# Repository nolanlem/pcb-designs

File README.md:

# pcb-designs
EAGLE PCB-DESIGN Files for Various Projects

Self-oscillating electromagnetic solenoid pendulums for kinetic art installation. 
+ this scalable circuit controls an array of solenoid electromagnets 
+ oscillatory motion using a a dynamic feedback control system. 
+ see audio-visual documentation [here](https://www.youtube.com/watch?v=IUg8T152WAE)

Magnetic Field -> Variable Frequency Oscillator and Voltage Controlled Amplifier design 
+ This circuit consists of 3 stages: a hall sensor + voltage buffer, sine wave oscillator + voltage buffer, and voltage controlled amplifier with variable signal power gain. 
+ video documentation [here](https://www.youtube.com/watch?v=2vKYp0yhHyw)

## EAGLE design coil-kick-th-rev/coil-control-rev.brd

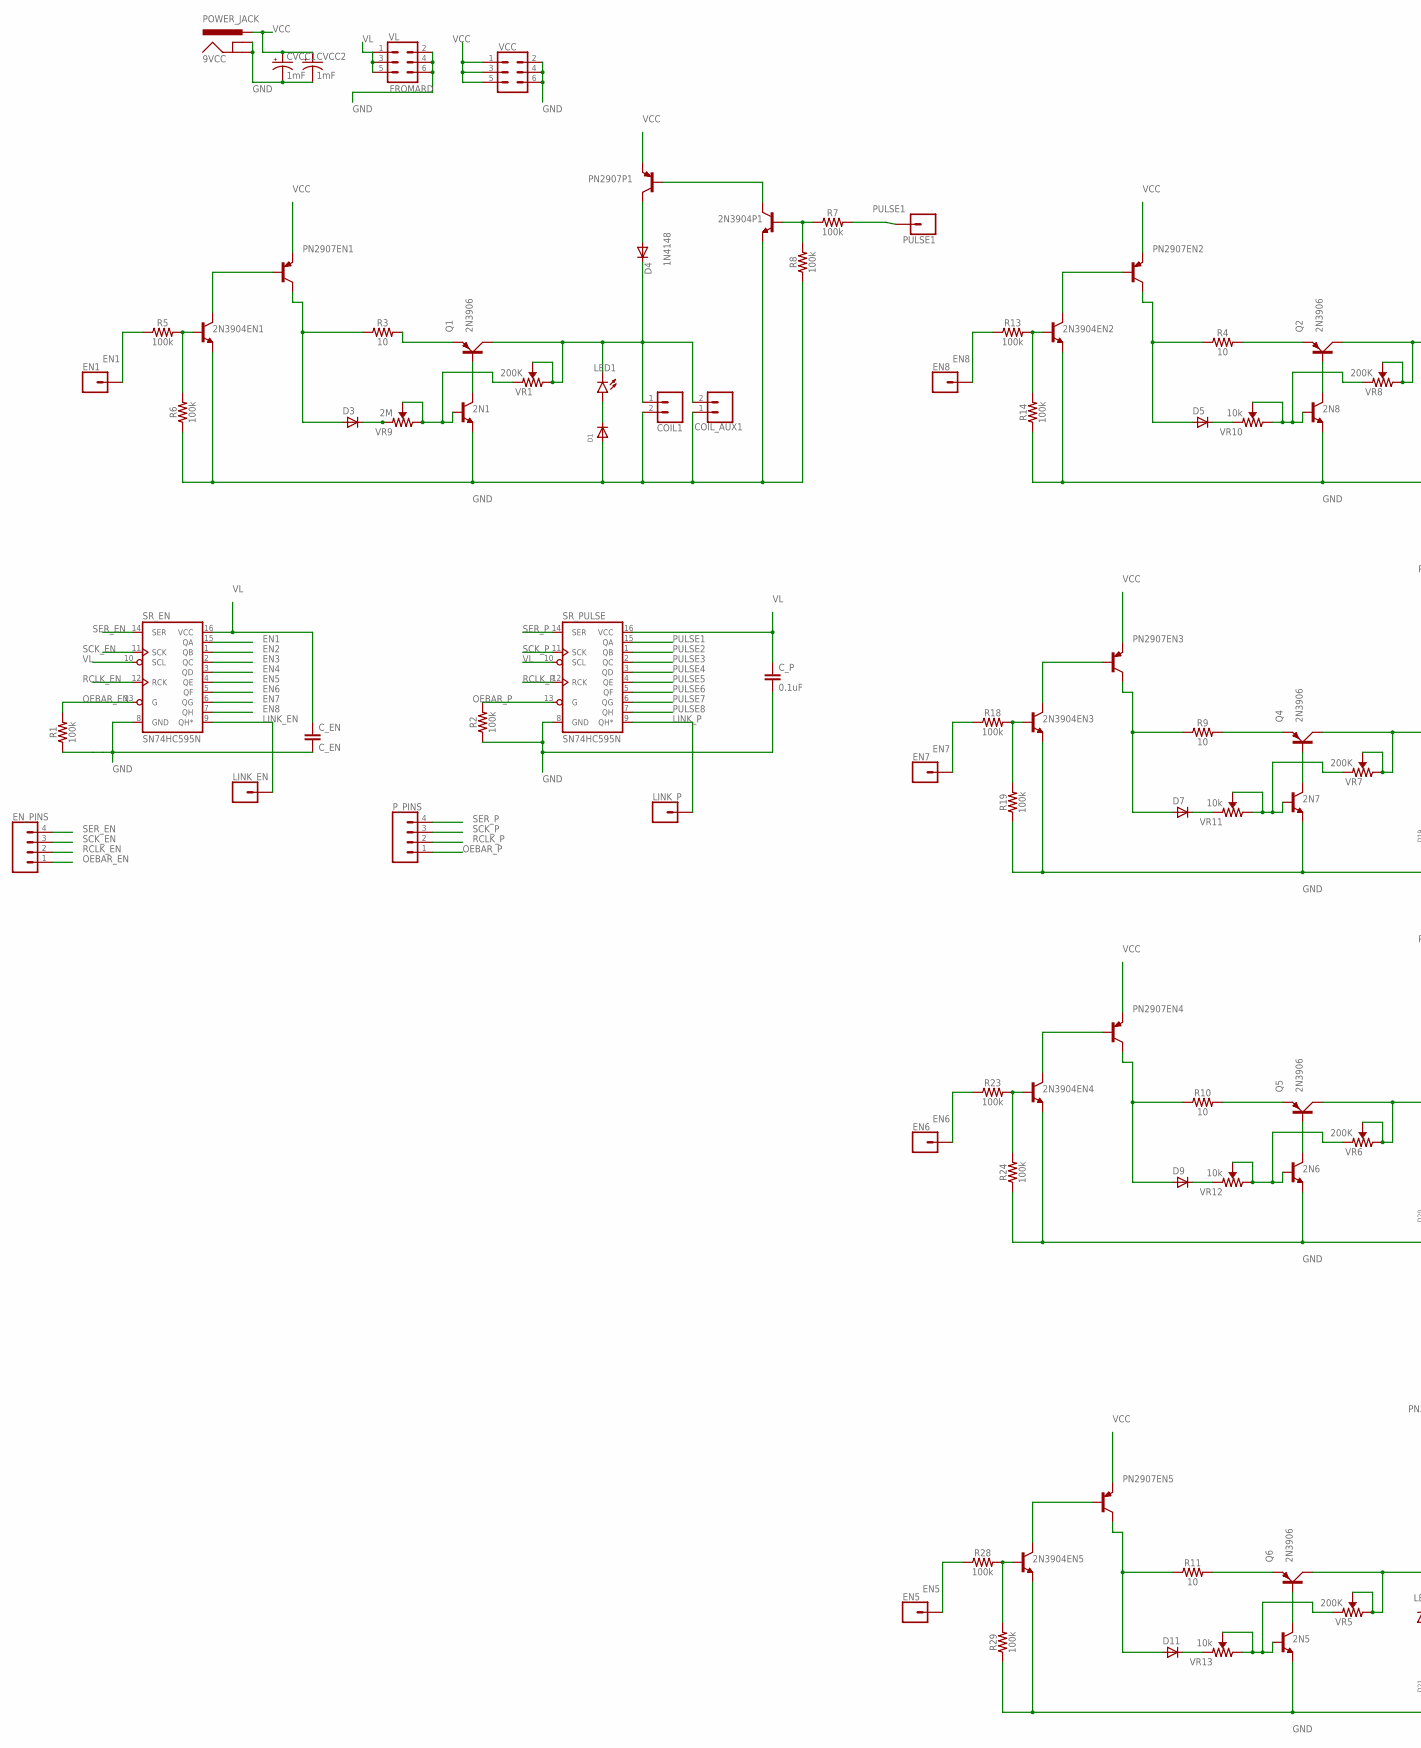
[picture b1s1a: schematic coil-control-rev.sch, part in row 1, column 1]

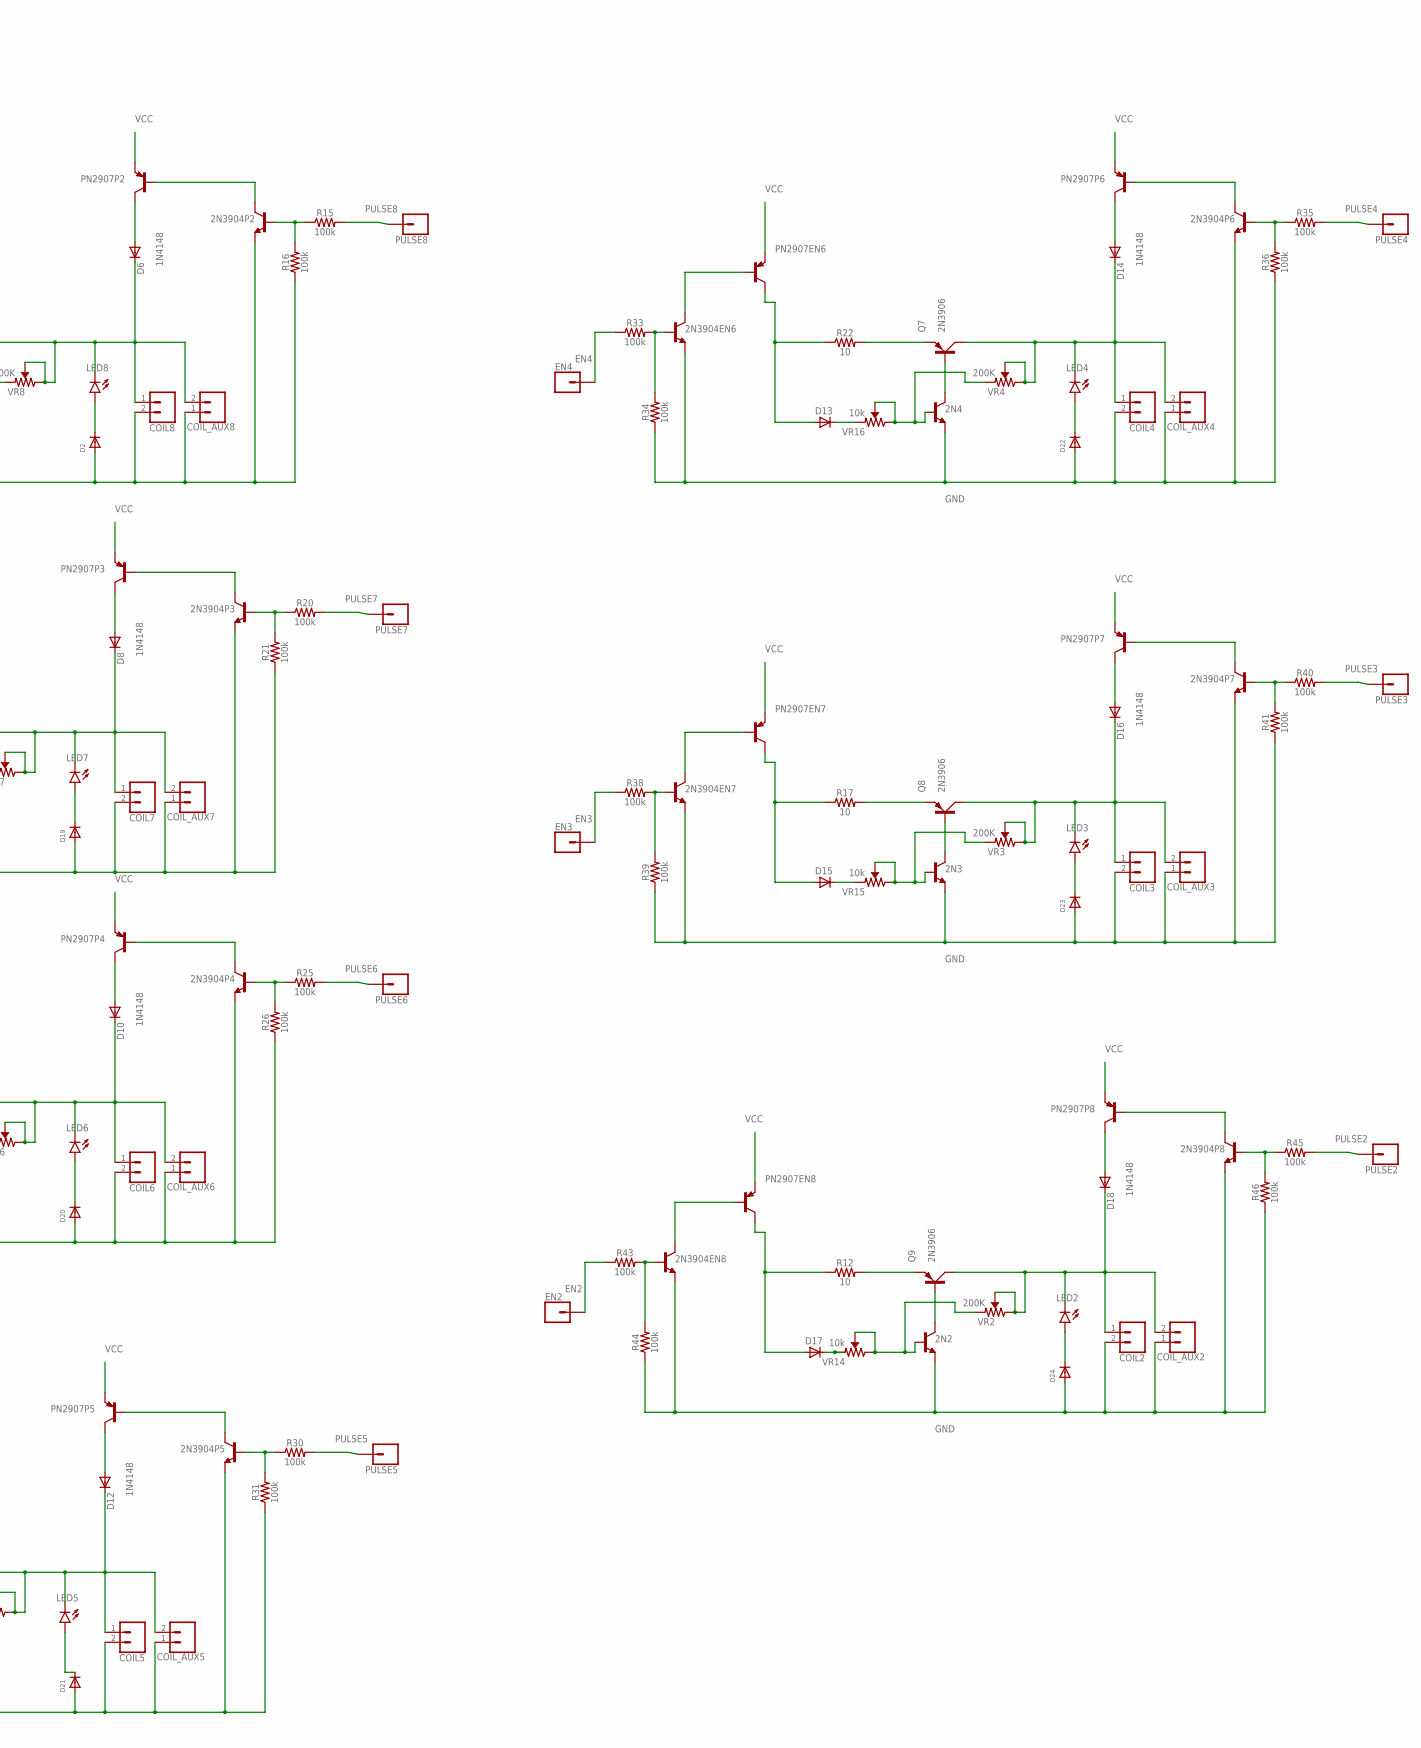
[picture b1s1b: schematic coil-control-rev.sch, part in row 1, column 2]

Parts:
2N1, 2N2, 2N3, 2N4, 2N5, 2N6, 2N7, 2N8: 2N2222; TO92-EBC-OVAL
2N3904EN1, 2N3904EN2, 2N3904EN3, 2N3904EN4, 2N3904EN5, 2N3904EN6, 2N3904EN7, 2N3904EN8, 2N3904P1, 2N3904P2, 2N3904P3, 2N3904P4, 2N3904P5, 2N3904P6, 2N3904P7, 2N3904P8: 2N3904; TO92
9VCC: POWER_JACK; POWER_JACK_PTH
COIL1, COIL2, COIL3, COIL4, COIL5, COIL6, COIL7, COIL8: CONN_02; 1X02
COIL_AUX1, COIL_AUX2, COIL_AUX3, COIL_AUX4, COIL_AUX5, COIL_AUX6, COIL_AUX7, COIL_AUX8: CONN_02; 1X02
CVCC1, CVCC2: 1mF; CPOL-RADIAL-5MM-10MM
C_EN: C_EN; CAP-PTH-SMALL-KIT
C_P: 0.1uF; CAP-PTH-SMALL-KIT
D1, D2, D3, D5, D7, D9, D13, D15, D17, D19, D20, D21, D22, D23, D24: DIODEDO-1N4148; DO-1N4148
D4, D6, D8, D10, D12, D14, D16, D18: 1N4148; DO-1N4148
D11: 200mA/100V/1V; DO-1N4148
EN1, EN2, EN3, EN4, EN5, EN6, EN7: CONN_01; 1X01
EN8: EN2; 1X01
EN_PINS: CONN_04PTH; 1X04
LED1, LED2, LED3, LED4, LED5, LED6, LED7, LED8: LED3MM; LED_3MM
LINK_EN: CONN_01; 1X01
LINK_P: CONN_01; 1X01
PN2907EN1, PN2907EN2, PN2907EN3, PN2907EN4, PN2907EN5, PN2907EN6, PN2907EN7, PN2907EN8, PN2907P1, PN2907P2, PN2907P3, PN2907P4, PN2907P5, PN2907P6, PN2907P7, PN2907P8: 2N2907; TO92-EBC-OVAL
PULSE1, PULSE2, PULSE3, PULSE4, PULSE5, PULSE6: CONN_01; 1X01
PULSE7: PULSE3; 1X01
PULSE8: PULSE2; 1X01
P_PINS: CONN_04PTH; 1X04
Q1, Q2, Q4, Q5, Q6, Q7, Q8, Q9: 2N3906; TO92D
R1, R2, R5, R6, R7, R8, R13, R14, R15, R16, R18, R19, R20, R21, R23, R24, R25, R26, R28, R29, R30, R31, R33, R34, R35, R36, R38, R39, R40, R41, R43, R44, R45, R46: 100k; AXIAL-0.3
R3, R4, R9, R10, R11, R12, R17, R22: 10; AXIAL-0.1
SR_EN: SN74HC595N; DIP16
SR_PULSE: SN74HC595N; DIP16
VCC: CONN_03X2NO_SILK; 2X3-NS
VL: FROMARD; 2X3
VR1, VR2, VR3, VR4, VR5, VR6, VR7, VR8: 200K; TRIMPOT-PTH-3386U
VR9: 2M; TRIMPOT-PTH-3386U
VR10, VR11, VR12, VR13, VR14, VR15, VR16: 10k; TRIMPOT-PTH-3386U

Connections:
EN1: EN1.1, R5.P$1 (1), SR_EN.15 (QA)
EN2: EN2.1, R43.P$1 (1), SR_EN.1 (QB)
EN3: EN3.1, R38.P$1 (1), SR_EN.2 (QC)
EN4: EN4.1, R33.P$1 (1), SR_EN.3 (QD)
EN5: EN5.1, R28.P$1 (1), SR_EN.4 (QE)
EN6: EN6.1, R23.P$1 (1), SR_EN.5 (QF)
EN7: EN7.1, R18.P$1 (1), SR_EN.6 (QG)
EN8: EN8.1, R13.P$1 (1), SR_EN.7 (QH)
GND: 2N1.E, 2N2.E, 2N3.E, 2N4.E, 2N5.E, 2N6.E, 2N7.E, 2N8.E, 2N3904EN1.3 (E), 2N3904EN2.3 (E), 2N3904EN3.3 (E), 2N3904EN4.3 (E), 2N3904EN5.3 (E), 2N3904EN6.3 (E), 2N3904EN7.3 (E), 2N3904EN8.3 (E), 2N3904P1.3 (E), 2N3904P2.3 (E), 2N3904P3.3 (E), 2N3904P4.3 (E), 2N3904P5.3 (E), 2N3904P6.3 (E), 2N3904P7.3 (E), 2N3904P8.3 (E), 9VCC.GND, 9VCC.GNDBREAK, COIL1.2, COIL2.2, COIL3.2, COIL4.2, COIL5.2, COIL6.2, COIL7.2, COIL8.2, COIL_AUX1.1, COIL_AUX2.1, COIL_AUX3.1, COIL_AUX4.1, COIL_AUX5.1, COIL_AUX6.1, COIL_AUX7.1, COIL_AUX8.1, CVCC1.-, CVCC2.-, C_EN.2, C_P.2, D1.A, D2.A, D19.A, D20.A, D21.A, D22.A, D23.A, D24.A, R1.P$1 (1), R2.P$1 (1), R6.P$1 (1), R8.P$1 (1), R14.P$1 (1), R16.P$1 (1), R19.P$1 (1), R21.P$1 (1), R24.P$1 (1), R26.P$1 (1), R29.P$1 (1), R31.P$1 (1), R34.P$1 (1), R36.P$1 (1), R39.P$1 (1), R41.P$1 (1), R44.P$1 (1), R46.P$1 (1), SR_EN.8 (GND), SR_PULSE.8 (GND), VCC.2, VCC.4, VCC.6, VL.2, VL.4, VL.6
LINK_EN: LINK_EN.1, SR_EN.9 (QH*)
LINK_P: LINK_P.1, SR_PULSE.9 (QH*)
unnamed: 2N3904EN2.1 (C), PN2907EN2.B
unnamed: 2N3904EN3.1 (C), PN2907EN3.B
unnamed: 2N3904EN1.1 (C), PN2907EN1.B
unnamed: 2N3904EN4.1 (C), PN2907EN4.B
unnamed: 2N3904EN5.1 (C), PN2907EN5.B
unnamed: 2N3904EN8.1 (C), PN2907EN8.B
unnamed: 2N1.B, VR1.1 (CCW), VR9.2 (WIPER), VR9.3 (CW)
unnamed: 2N3904EN7.1 (C), PN2907EN7.B
unnamed: D3.C, VR9.1 (CCW)
unnamed: 2N1.C, Q1.B
unnamed: D4.A, PN2907P1.C
unnamed: D3.A, PN2907EN1.C, R3.P$1 (1)
unnamed: 2N3904P1.2 (B), R7.P$1 (1), R8.P$2 (2)
unnamed: 2N3904P1.1 (C), PN2907P1.B
unnamed: 2N3904EN1.2 (B), R5.P$2 (2), R6.P$2 (2)
unnamed: 2N8.B, VR8.1 (CCW), VR10.2 (WIPER), VR10.3 (CW)
unnamed: 2N3904EN6.1 (C), PN2907EN6.B
unnamed: D5.C, VR10.1 (CCW)
unnamed: 2N8.C, Q2.B
unnamed: D6.A, PN2907P2.C
unnamed: D5.A, PN2907EN2.C, R4.P$1 (1)
unnamed: 2N3904P2.2 (B), R15.P$1 (1), R16.P$2 (2)
unnamed: 2N3904P2.1 (C), PN2907P2.B
unnamed: 2N3904EN2.2 (B), R13.P$2 (2), R14.P$2 (2)
unnamed: D9.C, VR12.1 (CCW)
unnamed: D7.C, VR11.1 (CCW)
unnamed: 2N7.C, Q4.B
unnamed: D8.A, PN2907P3.C
unnamed: D7.A, PN2907EN3.C, R9.P$1 (1)
unnamed: 2N3904P3.2 (B), R20.P$1 (1), R21.P$2 (2)
unnamed: 2N3904P3.1 (C), PN2907P3.B
unnamed: 2N3904EN3.2 (B), R18.P$2 (2), R19.P$2 (2)
unnamed: 2N6.B, VR6.1 (CCW), VR12.2 (WIPER), VR12.3 (CW)
unnamed: Q1.E, R3.P$2 (2)
unnamed: 2N6.C, Q5.B
unnamed: D10.A, PN2907P4.C
unnamed: D9.A, PN2907EN4.C, R10.P$1 (1)
unnamed: 2N3904P4.2 (B), R25.P$1 (1), R26.P$2 (2)
unnamed: 2N3904P4.1 (C), PN2907P4.B
unnamed: 2N3904EN4.2 (B), R23.P$2 (2), R24.P$2 (2)
unnamed: 2N5.B, VR5.1 (CCW), VR13.2 (WIPER), VR13.3 (CW)
unnamed: D11.C, VR13.1 (CCW)
unnamed: 2N5.C, Q6.B
unnamed: D12.A, PN2907P5.C
unnamed: D11.A, PN2907EN5.C, R11.P$1 (1)
unnamed: 2N3904P5.2 (B), R30.P$1 (1), R31.P$2 (2)
unnamed: 2N3904P5.1 (C), PN2907P5.B
unnamed: 2N3904EN5.2 (B), R28.P$2 (2), R29.P$2 (2)
unnamed: Q2.E, R4.P$2 (2)
unnamed: D13.C, VR16.1 (CCW)
unnamed: 2N4.C, Q7.B
unnamed: D14.A, PN2907P6.C
unnamed: D13.A, PN2907EN6.C, R22.P$1 (1)
unnamed: 2N3904P6.2 (B), R35.P$1 (1), R36.P$2 (2)
unnamed: 2N3904P6.1 (C), PN2907P6.B
unnamed: 2N3904EN6.2 (B), R33.P$2 (2), R34.P$2 (2)
unnamed: Q4.E, R9.P$2 (2)
unnamed: D15.C, VR15.1 (CCW)
unnamed: 2N3.C, Q8.B
unnamed: D16.A, PN2907P7.C
unnamed: D15.A, PN2907EN7.C, R17.P$1 (1)
unnamed: 2N3904P7.2 (B), R40.P$1 (1), R41.P$2 (2)
unnamed: 2N3904P7.1 (C), PN2907P7.B
unnamed: 2N3904EN7.2 (B), R38.P$2 (2), R39.P$2 (2)
unnamed: Q5.E, R10.P$2 (2)
unnamed: D17.C, VR14.1 (CCW)
unnamed: 2N2.C, Q9.B
unnamed: D18.A, PN2907P8.C
unnamed: D17.A, PN2907EN8.C, R12.P$1 (1)
unnamed: 2N3904P8.2 (B), R45.P$1 (1), R46.P$2 (2)
unnamed: 2N3904P8.1 (C), PN2907P8.B
unnamed: 2N3904EN8.2 (B), R43.P$2 (2), R44.P$2 (2)
unnamed: 2N3.B, VR3.1 (CCW), VR15.2 (WIPER), VR15.3 (CW)
unnamed: 2N7.B, VR7.1 (CCW), VR11.2 (WIPER), VR11.3 (CW)
unnamed: 2N2.B, VR2.1 (CCW), VR14.2 (WIPER), VR14.3 (CW)
unnamed: 2N4.B, VR4.1 (CCW), VR16.2 (WIPER), VR16.3 (CW)
unnamed: Q6.E, R11.P$2 (2)
unnamed: Q9.E, R12.P$2 (2)
unnamed: Q8.E, R17.P$2 (2)
unnamed: Q7.E, R22.P$2 (2)
unnamed: D1.C, LED1.A
unnamed: D2.C, LED8.A
unnamed: D19.C, LED7.A
unnamed: D20.C, LED6.A
unnamed: D21.C, LED5.A
unnamed: D24.C, LED2.A
unnamed: D23.C, LED3.A
unnamed: D22.C, LED4.A
OEBAR_EN: EN_PINS.1, R1.P$2 (2), SR_EN.13 (G)
OEBAR_P: P_PINS.1, R2.P$2 (2), SR_PULSE.13 (G)
PULSE1: PULSE1.1, R7.P$2 (2), SR_PULSE.15 (QA)
PULSE2: PULSE2.1, R45.P$2 (2), SR_PULSE.1 (QB)
PULSE3: PULSE3.1, R40.P$2 (2), SR_PULSE.2 (QC)
PULSE4: PULSE4.1, R35.P$2 (2), SR_PULSE.3 (QD)
PULSE5: PULSE5.1, R30.P$2 (2), SR_PULSE.4 (QE)
PULSE6: PULSE6.1, R25.P$2 (2), SR_PULSE.5 (QF)
PULSE7: PULSE7.1, R20.P$2 (2), SR_PULSE.6 (QG)
PULSE8: PULSE8.1, R15.P$2 (2), SR_PULSE.7 (QH)
RCLK_EN: EN_PINS.2, SR_EN.12 (RCK)
RCLK_P: P_PINS.2, SR_PULSE.12 (RCK)
S2: COIL1.1, COIL_AUX1.2, D4.C, LED1.K (C), Q1.C, VR1.2 (WIPER), VR1.3 (CW)
S3: COIL8.1, COIL_AUX8.2, D6.C, LED8.K (C), Q2.C, VR8.2 (WIPER), VR8.3 (CW)
S4: COIL7.1, COIL_AUX7.2, D8.C, LED7.K (C), Q4.C, VR7.2 (WIPER), VR7.3 (CW)
S5: COIL6.1, COIL_AUX6.2, D10.C, LED6.K (C), Q5.C, VR6.2 (WIPER), VR6.3 (CW)
S6: COIL5.1, COIL_AUX5.2, D12.C, LED5.K (C), Q6.C, VR5.2 (WIPER), VR5.3 (CW)
S7: COIL4.1, COIL_AUX4.2, D14.C, LED4.K (C), Q7.C, VR4.2 (WIPER), VR4.3 (CW)
S8: COIL3.1, COIL_AUX3.2, D16.C, LED3.K (C), Q8.C, VR3.2 (WIPER), VR3.3 (CW)
S9: COIL2.1, COIL_AUX2.2, D18.C, LED2.K (C), Q9.C, VR2.2 (WIPER), VR2.3 (CW)
SCK_EN: EN_PINS.3, SR_EN.11 (SCK)
SCK_P: P_PINS.3, SR_PULSE.11 (SCK)
SER_EN: EN_PINS.4, SR_EN.14 (SER)
SER_P: P_PINS.4, SR_PULSE.14 (SER)
VCC: 9VCC.PWR, CVCC1.+, CVCC2.+, PN2907EN1.E, PN2907EN2.E, PN2907EN3.E, PN2907EN4.E, PN2907EN5.E, PN2907EN6.E, PN2907EN7.E, PN2907EN8.E, PN2907P1.E, PN2907P2.E, PN2907P3.E, PN2907P4.E, PN2907P5.E, PN2907P6.E, PN2907P7.E, PN2907P8.E, VCC.1, VCC.3, VCC.5
VL: C_EN.1, C_P.1, SR_EN.10 (SCL), SR_EN.16 (VCC), SR_PULSE.10 (SCL), SR_PULSE.16 (VCC), VL.1, VL.3, VL.5

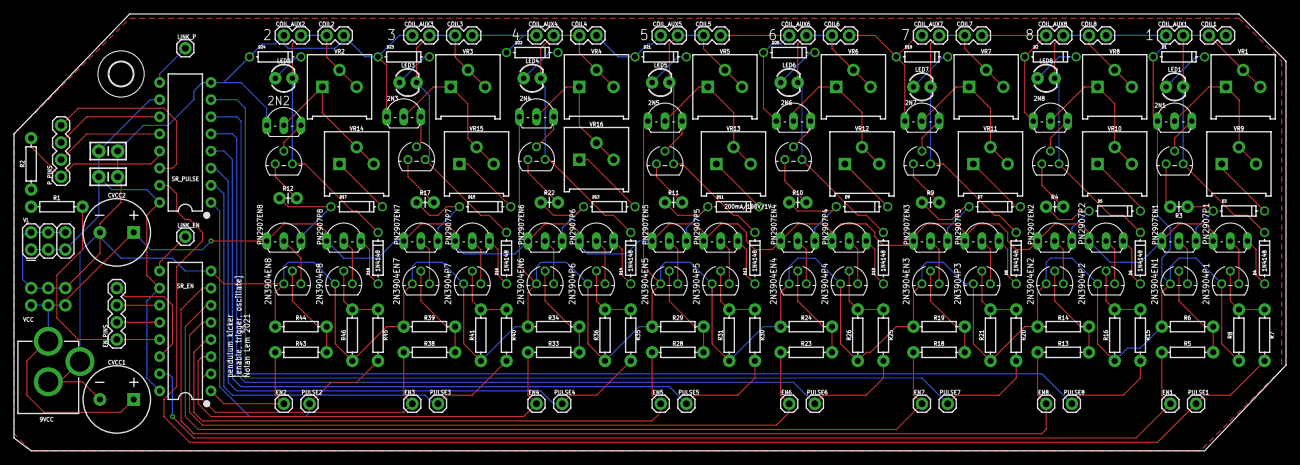
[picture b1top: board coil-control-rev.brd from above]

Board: 2 copper layers, 188.6 x 64.8 mm, 184 parts (0 on the bottom side), 125 nets.

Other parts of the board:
U$1: 3,6

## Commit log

2022-06-22 added single image
2022-07-06 updated with vca push pole

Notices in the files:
parts and their libraries:
SparkFun-Connectors: Licensing: Creative Commons ShareAlike 4.0 International - https://creativecommons.org/licenses/by-sa/4.0
